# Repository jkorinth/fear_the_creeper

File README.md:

# Creeper Gadget

![Creeper][creeper.png]

A toy gadget that produces light + sound effects like a Creeper in Minecraft.
Fun little project which covers software, electronics, mechanical design elements.
And Mincraft. :)

## Hardware

* 35mm x 35mm 2-layer PCB w/dedicated ground plane
* Microcontroller: ATtiny85
* CR23xx battery
* Accelerometer: IIS328DQTR (low power, interrupt)
* piezzo buzzer
* 2x discrete LEDs (LP T67F)
* battery holder
* On/Off switch

## Mechanical

* 3D printed 40mm x 40mm x 10mm case
* cutout at Creeper "face" reveals black PCB underneath
* snap-fit lid for battery replacement
* hanger bracket for keyrings or lanyards

## Software

* IRQ-triggered sequence on motion detection
* fuse ignition sounds
* accelerating blinking
* explosion sound

## Tools

* Electronic Design: KiCAD
* Mechanical Design: FreeCAD
* Software Design: Arduino

## Current State ✅❌

### Summary
* i2c via I2CTinyBB: ✅
* irqs from IIS328DQ: ✅
* ISP: ✅
* LEDs: ✅
* KiBot CI/CD: kinda
* buzzer: ❌
* wake from sleep: ❌
* tilt switch: ❌

### Issues / Next Steps
Idea with the analog switch (74HC4066BQ) was nice, but it creates several new
problems: In closed state it has a small resistance (70R-180R), which creates
an accidental voltage divider with a pull-up on the line. Signal integrity was
good enough for i2c, strange enough, but both INT and BUZ suffered severe
issues when traversing the switch. The wake-up from deep sleep works fine when
bridging the `I2C` and `I2C_MCU` nets, but then ISP no longer works (which was
the whole point of having the analog switch in the first place).

The tilt switch has the issue that it generates only very short pulses, which
don't reliably wake up the MCU. Simplest solution would be a small capacitor
which slows down the rising edge, but I haven't tried that yet. Or a flip-flop
but that seems like total overkill.

This ISP issue is bugging me and I want to solve it. My next attempt would be
to use MOSFETs: 1x P-channel for the +3V pullups on SCL and SDA, 3x N-channel
for the SCL, SDA and INT signals. Costs more board space, but if I can use sth
like SOT-323, it may not be significant (also, the 74HC4066BQ footprint would
be gone, freeing up some little space).

Other issues:
  1. The power switch doesn't break the circuit from the debug connector.
  2. Add testpoints to make debugging less painful.

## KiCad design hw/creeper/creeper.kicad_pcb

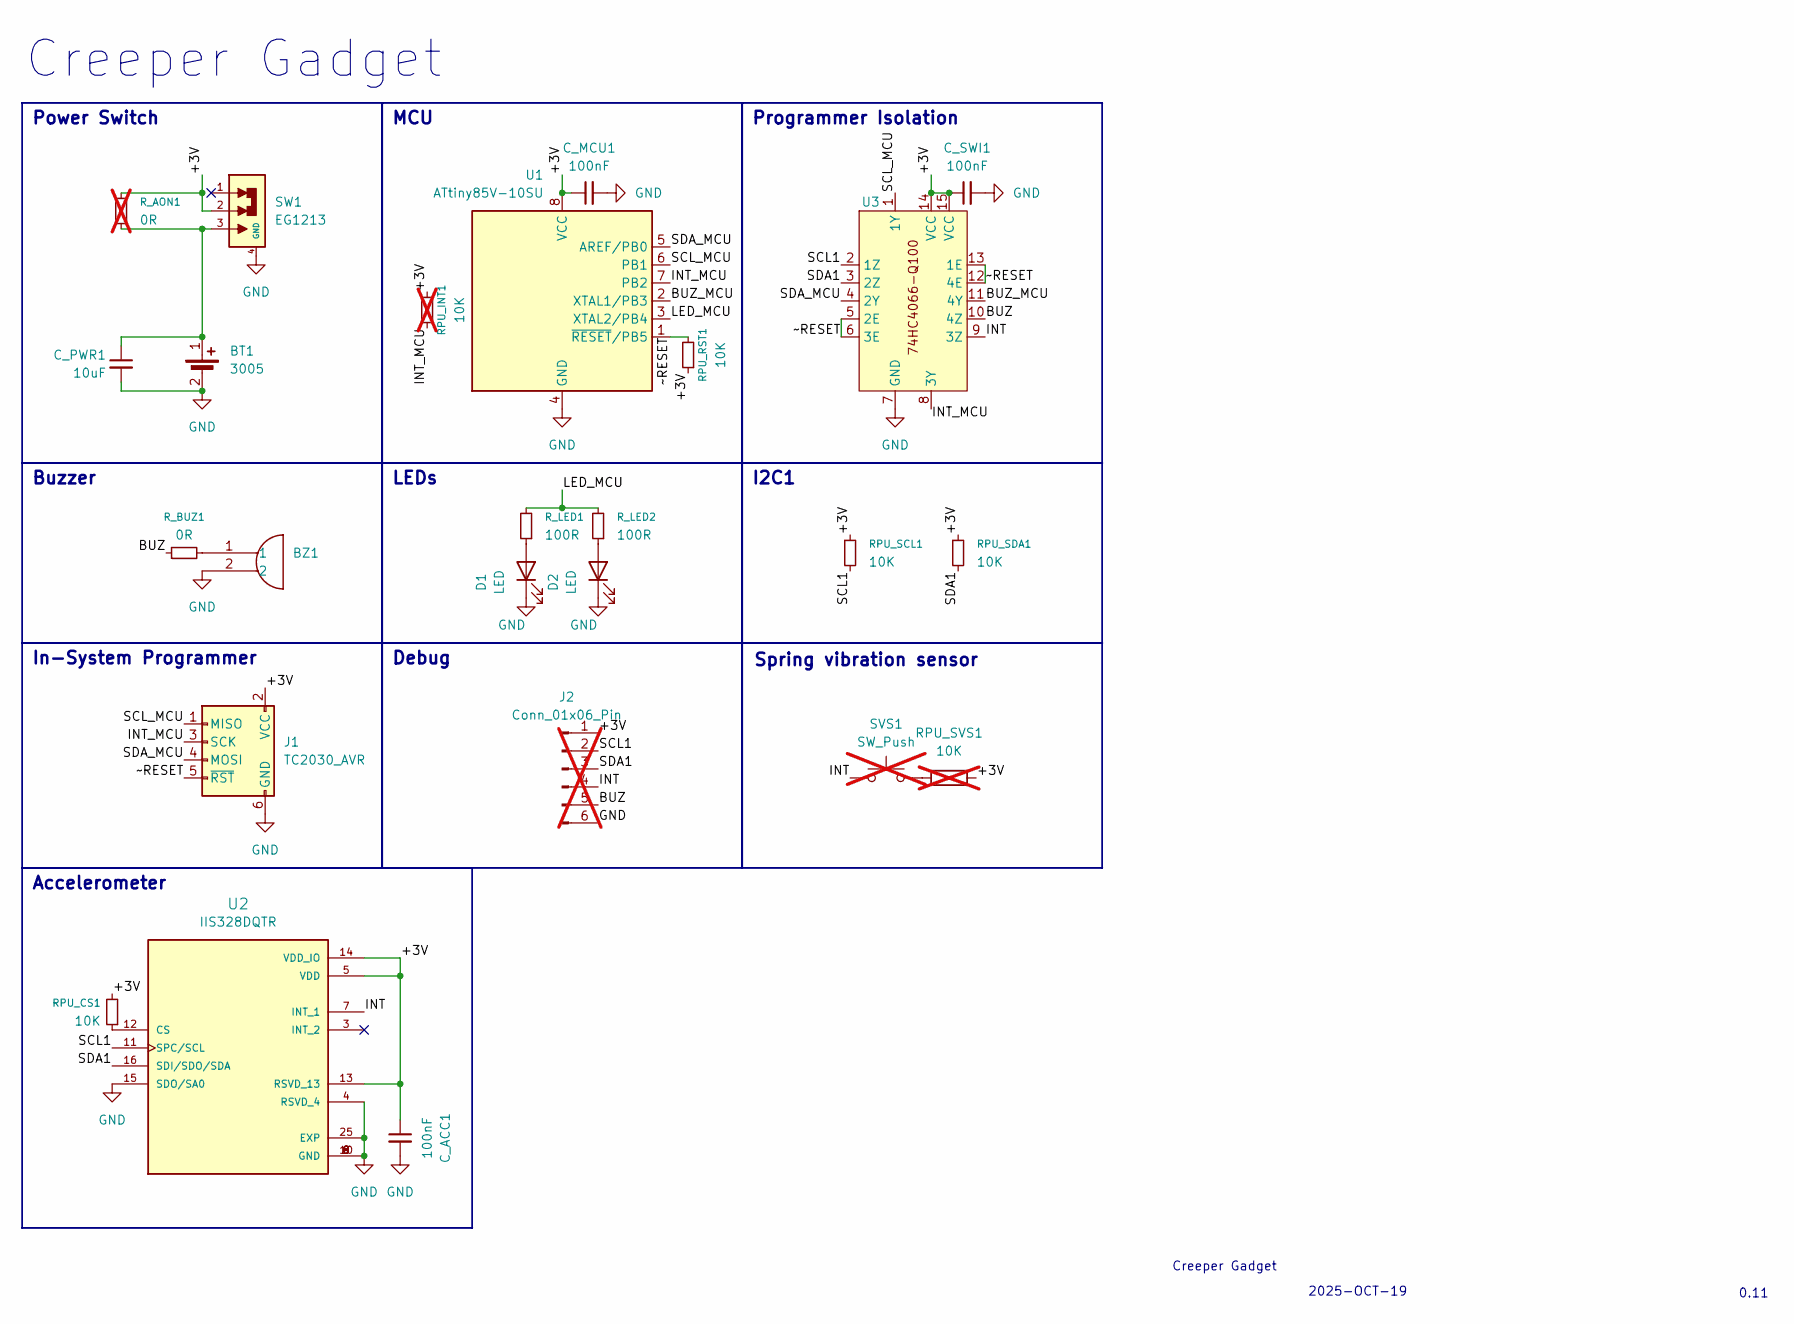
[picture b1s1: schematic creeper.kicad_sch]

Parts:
BT1: 3005; BAT_3005; MPN 3005
BZ1: XDCR_SMT-0825-S-2-R
C_ACC1: 100nF; C_0603_1608Metric_Pad1.08x0.95mm_HandSolder; MPN C0603C101K3RACTU
C_MCU1: 100nF; C_0603_1608Metric_Pad1.08x0.95mm_HandSolder; MPN C0603C101K3RACTU
C_PWR1: 10uF; C_0805_2012Metric_Pad1.18x1.45mm_HandSolder; MPN GRM21BZ71E106KE15L
C_SWI1: 100nF; C_0603_1608Metric_Pad1.08x0.95mm_HandSolder; MPN C0603C101K3RACTU
D1, D2: LED; LED_LG_T671-L2N1-1-Z; MPN LG T67F-R1T1-24-1-20-R18-Z
J1: TC2030_AVR; CON_TC2030_outlined
J2: Conn_01x06_Pin; PinHeader_1x06_P2.54mm_Vertical; not fitted
RPU_CS1: 10K; R_0603_1608Metric_Pad0.98x0.95mm_HandSolder; MPN CRCW060310K0JNEA
RPU_INT1: 10K; R_0603_1608Metric_Pad0.98x0.95mm_HandSolder; MPN CRCW060310K0JNEA; not fitted
RPU_RST1: 10K; R_0603_1608Metric_Pad0.98x0.95mm_HandSolder; MPN CRCW060310K0JNEA
RPU_SCL1: 10K; R_0603_1608Metric_Pad0.98x0.95mm_HandSolder; MPN CRCW060310K0JNEA
RPU_SDA1: 10K; R_0603_1608Metric_Pad0.98x0.95mm_HandSolder; MPN CRCW060310K0JNEA
RPU_SVS1: 10K; R_0603_1608Metric_Pad0.98x0.95mm_HandSolder; not fitted
R_AON1: 0R; R_0603_1608Metric_Pad0.98x0.95mm_HandSolder; not fitted
R_BUZ1: 0R; R_0603_1608Metric_Pad0.98x0.95mm_HandSolder; MPN CRCW06030000Z0EA
R_LED1, R_LED2: 100R; R_0603_1608Metric_Pad0.98x0.95mm_HandSolder; MPN CRCW060343R0JNEA
SVS1: SW_Push; SW_180xxP_Spring_Vibration_Sensor; not fitted
SW1: EG1213; SW_EG1213; MPN EG1213
U1: ATtiny85V-10SU; SOIC-8_5.3x5.3mm_P1.27mm; MPN ATTINY85V-10SU
U2: IIS328DQTR; IIS328DQTR_QFN50P400X400X185-25N; PARTREV 3; DigiKey_Part_Number 497-15701-1-ND
U3: QFN50P300X250X100-15N; MPN 74HC4066BQ-Q100,11

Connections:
/+3V: C_ACC1.1, C_MCU1.1, C_SWI1.1, J1.2 (VCC), J2.1, RPU_CS1.2, RPU_INT1.2, RPU_RST1.1, RPU_SCL1.1, RPU_SDA1.1, RPU_SVS1.2, R_AON1.1, SW1.2, U1.8 (VCC), U2.5 (VDD), U2.13 (RSVD_13), U2.14 (VDD_IO), U3.14 (VCC), U3.15 (VCC)
/BUZ: J2.5, R_BUZ1.1, U3.10 (4Z)
/BUZ_MCU: U1.2 (XTAL1/PB3), U3.11 (4Y)
/INT: J2.4, SVS1.1, U2.7 (INT_1), U3.9 (3Z)
/INT_MCU: J1.3 (SCK), RPU_INT1.1, U1.7 (PB2), U3.8 (3Y)
/LED_MCU: R_LED1.2, R_LED2.2, U1.3 (XTAL2/PB4)
/SCL1: J2.2, RPU_SCL1.2, U2.11 (SPC/SCL), U3.2 (1Z)
/SCL_MCU: J1.1 (MISO), U1.6 (PB1), U3.1 (1Y)
/SDA1: J2.3, RPU_SDA1.2, U2.16 (SDI/SDO/SDA), U3.3 (2Z)
/SDA_MCU: J1.4 (MOSI), U1.5 (AREF/PB0), U3.4 (2Y)
/~RESET: J1.5 (~RST), RPU_RST1.2, U1.1 (~RESET/PB5), U3.5 (2E), U3.6 (3E), U3.12 (4E), U3.13 (1E)
GND: BT1.2 (-), BZ1.2, C_ACC1.2, C_MCU1.2, C_PWR1.2, C_SWI1.2, D1.1 (K), D2.1 (K), J1.6 (GND), J2.6, SW1.4 (GND), U1.4 (GND), U2.4 (RSVD_4), U2.6 (GND), U2.8 (GND), U2.9 (GND), U2.10 (GND), U2.15 (SDO/SA0), U2.25 (EXP), U3.7 (GND)
unnamed: BT1.1 (+), C_PWR1.1, R_AON1.2, SW1.3
unnamed: BZ1.1, R_BUZ1.2
unnamed: D1.2 (A), R_LED1.1
unnamed: D2.2 (A), R_LED2.1
unnamed: RPU_SVS1.1, SVS1.2
unnamed: RPU_CS1.1, U2.12 (CS)

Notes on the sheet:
LEDs
Creeper Gadget
MCU
Creeper Gadget
I2C1
2025-OCT-19
Buzzer
Debug
Power Switch
Programmer Isolation
In-System Programmer
0.11
Spring vibration sensor
Accelerometer

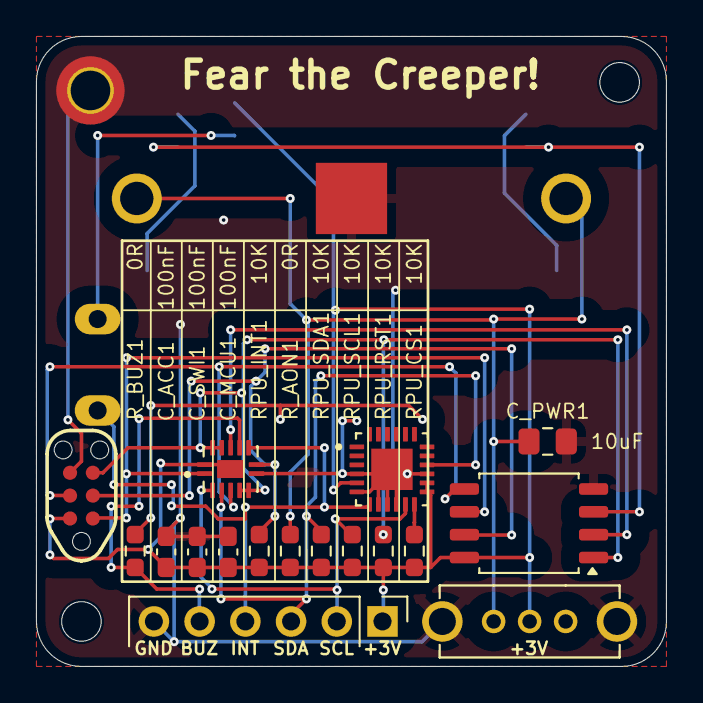
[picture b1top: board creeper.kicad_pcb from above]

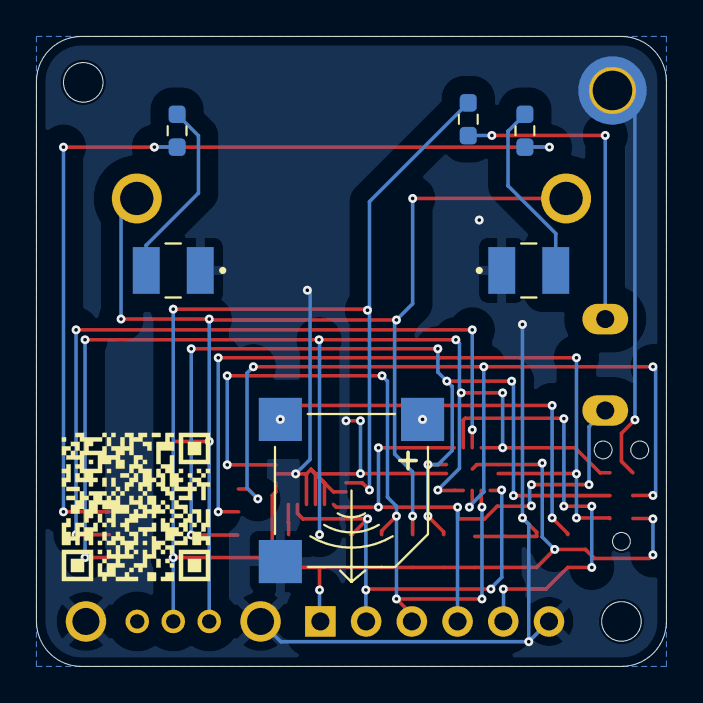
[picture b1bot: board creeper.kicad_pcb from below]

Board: 2 copper layers, 35.0 x 35.0 mm, 26 parts (8 on the bottom side), 18 nets.

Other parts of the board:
QR1: https://github.com/jkorinth/fear_the_creeper; github_jkorinth-fear_the_creeper

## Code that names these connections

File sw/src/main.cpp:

#include <Arduino.h>
#include <I2CTinyBB.h>
#include <avr/interrupt.h>
#include <avr/power.h>
#include <avr/sleep.h>
#include "iis328dq.h"

#define INT 2
#define BUZ 3
#define LED 4

#define IIS328DQ_ADDR 0x18
#define REG_WHO_AM_I 0x0f
#define REG_CTRL_REG1 0x20

#define ARR_SZ(x) (sizeof((x)) / sizeof(*(x)))

volatile int _play = 1;

void iis328dq_init()
{
	uint8_t d = 0;
	for (size_t i = 0; i < IIS328DQ_INIT_COUNT; ++i) {
		uint8_t tmp[2] = { iis328dq_shake_init[i].reg, iis328dq_shake_init[i].value };
		I2CWrite(IIS328DQ_ADDR, tmp, 2);
		I2CReadReg(IIS328DQ_ADDR, tmp[0], &d, 1);
	}
}

void setup() {
  uint8_t d;
  clock_prescale_set(clock_div_1);
  DDRB = (1 << PB4) | (1 << PB3) | (1 << PB1) | (1 << PB0);
  PORTB = 0;
  MCUCR = 0; // low level-triggered interrupt
  GIMSK |= (1 << INT0);  // Enable INT0 external interrupt
  I2CInit(0, 1, 10);
  sei();
  iis328dq_init();
}

// Interrupt Service Routine for INT0
ISR(INT0_vect) {}

void enterSleep() {
  uint8_t d = 0;
  MCUCR = 0;
  GIMSK |= (1 << INT0);  // Enable INT0 external interrupt
  
  set_sleep_mode(SLEEP_MODE_PWR_DOWN);  // Set deep sleep mode
  sleep_enable();  // Enable sleep bit
  sei();  // Enable global interrupts
  sleep_cpu();  // Go to sleep - execution stops here
  
  // Code resumes here after wake-up
  sleep_disable();  // Disable sleep bit
  GIMSK &= ~(1 << INT0);  // disable INT0 external interrupt
  I2CReadReg(IIS328DQ_ADDR, IIS328DQ_INT1_SRC, &d, 1);
  _play = 1;
}

void play()
{
	int countdown = 700;
	while (countdown > 0) {
		digitalWrite(LED, HIGH);
		delay(25);
		digitalWrite(LED, LOW);
		countdown *= 0.84;
		delay(countdown);
	}
	_play = 0;
}

void loop() {
	if (_play) {
		play();
	}
	enterSleep();
}

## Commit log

2025-07-14 docs(README): add design details in summary
2025-08-20 feat: create dev environments for different subsections
2025-08-20 feat(pcb): first manufactured PCB version
2025-08-20 bump: version 0.5.9 → 0.6.0
2025-08-20 add first drafts for 3D printed cases
2025-08-20 feat(pcb): v0.7
    * added TC2030_AVR pogo debug plug connector
    * added isolating resistors to stabilize ISP
    * fixed missing connections of battery holder
    * added 0R bridge for always-on w/o switch
    * moved mounting hole out of case opening
    * did manual place and route
2025-08-20 bump: version 0.6.0 → 0.7.0
2025-10-01 feat: rev. 0.10: use analog switch for programmer isolation
2025-10-01 feat(flakes): update flakes and add tools
2025-10-02 feat(pcb): update constraints, fix via sizes
2025-10-02 feat(sw): prepare initial setup with pio and simavr
2025-10-02 fix(flake): update flake for sw
2025-10-19 feat: v0.11: replace accelerometer with optional spring vibration sensor
2025-11-01 build(tools): add gtkwave, pulseview
2025-11-01 fix(pcb): remove solder mask margin from pins
    BREAKING CHANGE:
2025-11-01 fix(sch+pcb): update footprints, reset DNP
2025-11-01 fix(sw): WIP: software for IIS328DQ build
    * weird glitches, INT and INT_MCU seem to differ
    * maybe a capacitance issue, the INT_MCU dropping much slower than INT
2025-11-01 fix(pcb): sync'ed footprints back, excluded mounting hole footprints
2025-11-02 ci(kibot): add KiBot configuration and fix some minor issues
2025-11-02 ci(gh): add workflow
2025-11-02 build(tools): add kbcli command to start local KiBot
2025-11-02 fix(sw): add missing submodule for I2CTinyBB
2025-11-02 docs(REAMDE.md): update
2025-11-02 style(hw): gitignore: ignore .cache
2026-01-18 refactor(scripts): make_interval_table.py: make executable
2026-01-18 docs(README.md): upload creeper head image
